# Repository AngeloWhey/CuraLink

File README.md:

# CuraLink

Four-channel **benchtop neural-signal acquisition prototype** with a custom analog front end, STM32WBA52/BLE telemetry, and battery-buffered 13.56 MHz wireless charging. This repository is the engineering handoff for moving computers: editable schematics and PCB, ADS cells, circuit models, simulations, calculations, sourcing evidence and decision history belong together.

**Current build, 2026-11-22.** Use the [plain-text builder handoff](docs/BUILD-NEXT.txt), the [recommended low-capacitance electronics design](hardware/rev-a/bench-four-coax-low-c/README.md) and the [TX/RX matching schematics and parts](hardware/wpt/bench-rf/README.md). The revised bench board uses four U.FL inputs, a packaged rectifier and live BLE charger status. An externally charged qualified pack can power a signal-only test with WPT disconnected. The native designs and simulation evidence are engineering candidates. Routing, sourcing at order time, real-pack qualification, firmware and hardware validation govern release.

**Migration handoff and follow-up ADS review: 2026-11-22, America/New_York.** The complete migration batch was pushed and verified through a fresh GitHub/LFS download. A subsequent [fresh ADS review](hardware/wpt/ads/review-2026-11-22/README.md) checks the fixed paper coils, nonlinear power demand and translated AFE DC/AC behavior. That review used the earlier eight-channel hardware. The four-channel handoff above includes fresh KiCad checks, a dated BOM/stock audit and packaged-bridge power simulations. The design is an engineering **Candidate**, with no fabrication release, completed firmware or recorded CuraLink hardware measurements.

## Start here

1. Read the [engineering handbook](docs/engineering-handbook.md): accepted requirements, decision IDs, rationale and unresolved gates. Its status vocabulary governs the project.
2. Follow [moving to a new computer](docs/moving-computers.md) for Git LFS, tool setup, dataset restoration and file paths.
3. Open the [low-capacitance four-channel KiCad project](hardware/rev-a/bench-four-coax-low-c/curalink-rev-a.kicad_pro) to continue layout. Its [schematic PDF](hardware/rev-a/bench-four-coax-low-c/schematic.pdf) is readable without CAD. The TLV-only four-coax variant and original eight-channel board are comparison designs.
4. Open [ads/MyWorkspace_wrk](ads/MyWorkspace_wrk) and select **MyLibrary_lib → CuraLink_RX_BAS4002A_HB → schematic** for the packaged receiver. The [schematic PDF and HB results](hardware/wpt/ads/native-packaged-bridge/) and [full load/sensitivity study](hardware/wpt/ads/receiver-ic-review-2026-11-22/) can be read without ADS.

## Where the work stands

| Area | Current context |
|---|---|
| Signal specification | Four U.FL channels plus local shared REF. Drive each coax from a low-impedance calibrated generator and place its nominal 47 kΩ emulator at the board end. The retained input baseline is 200 µVpp over approximately 300 Hz–7 kHz. |
| Acquisition choice | The accepted historical baseline uses analog event detection with the MCU ADC unused. The current editable Rev A schematic **recommends ADC acquisition and digital detection** on the same STM32WBA52 family. That replacement remains Candidate under D-024; it is not a silently accepted requirement change. |
| AFE candidate | Five MAX44280 gain-11 preamps, four TLV-based filter chains and a separate high-value bias return. At 0.60 pF of added layout capacitance per input, the stressed model clears 10.70 MΩ across 300 Hz–7 kHz. At 1.00 pF it falls to 9.16 MΩ. Actual routed-board impedance is a release requirement. |
| Telemetry | STM32WBA52 with a ceramic BLE antenna; firmware, ADC/BLE continuity, antenna/RF implementation and measured power remain open. |
| Operating modes | RECORD powers the AFE and MCU from a qualified battery or emulator. During a wireless charge test, the AFE is off and the MCU reports charging status over BLE when the receiver can sustain it. |
| Charger/cell baseline | BQ25185 charger. The lab LiPo, connector and settings await identification. The historical 55 mAh cell and 20 mA/4.1 V example are separate from release limits. Battery-only tests can proceed independently. |
| Wireless receiver | Published Luo 13.56 MHz coil geometry and nominal 10 mm gap, Infineon packaged bridge and TPS70950 5 V LDO. Fixed-coil HB, nonlinear load and regulator transient results are available as tables. RF power capability, off-axis delivery, RF capacitor loss and heating remain to be verified. |
| Physical CAD | Separate four-channel KiCad schematic and 80 × 74 mm unrouted placement for the low-capacitance design, plus TX/RX matching/receiver sheets. Complete manual routing, RF and shield returns, antenna-edge clearance and assembly checks. |
| Manufacturing | The low-capacitance BOM had 73 fitted SKUs stocked at LCSC for one electronics board. The TX/RX parts and four cables were checked separately. Combined minimum-order parts cost US$102.85 on 2026-11-22. Cell, delivered assembly price and hardware verification remain open. |

## Files to open

| Path | Contents and role |
|---|---|
| [docs/engineering-handbook.md](docs/engineering-handbook.md) | Central decision record; read before changing the design. |
| [hardware/rev-a/](hardware/rev-a/README.md) | Editable KiCad project, all schematic sheets, PCB, project symbols/footprints, BOM and physical pin/net tables. |
| [hardware/rev-a/afe/](hardware/rev-a/afe/AFE-design-review.md) | AFE topology, gain/noise/loading calculations and model boundaries. |
| [hardware/rev-a/power/](hardware/rev-a/power/power-design.md) | Charging, hardware mode isolation, cell/temperature protection candidates, rails and power budget. |
| [hardware/rev-a/mcu/](hardware/rev-a/mcu/mcu-design.md) | MCU, ADC/BLE, clock, RF and antenna integration. |
| [hardware/rev-a/ltspice/](hardware/rev-a/ltspice/README.md) | Actual DC/AC/startup/recovery and bounded protection simulations, models, logs and result reports. |
| [hardware/rev-a/signal-integrity/](hardware/rev-a/signal-integrity/README.md) | Crosstalk/bias studies, sensitive regions and package/RF/layout audits. |
| [hardware/rev-a/pcb/](hardware/rev-a/pcb/README.md) | Footprints, placement, connectivity checks and incomplete routing status. |
| [ads/MyWorkspace_wrk/](ads/MyWorkspace_wrk) and [ADS migration notes](ads/README.md) | Native ADS workspace and `MyLibrary_lib`, large-dataset restoration and legacy model/display relocation. Open the whole workspace. |
| [hardware/wpt/ads/](hardware/wpt/ads/README.md) | ADS setup, model provenance, standalone fixtures, search/sweep results and charger-load guidance. |
| [2026-11-22 ADS verification](hardware/wpt/ads/review-2026-11-22/README.md) | Fresh 71.873% passive-link check, 48 authored-load HB cases, DC compliance and full AFE DC/AC evidence; explicit remaining build gates. |
| [hardware/wpt/models/](hardware/wpt/models/README.md) | Calculated Touchstone derived from published nominal coil parameters; not original measured S2P data. |
| [procurement/](procurement) and [Rev A procurement](hardware/rev-a/procurement) | Dated LCSC responses, sourcing checks and cost evidence. |
| [tools/](tools) | CAD generation/verification, analysis and packaging scripts. Read their output paths before running generators. |
| [output/](output) | Earlier handoff archive and checksum, preserved with Git LFS. Later source/report changes can supersede this historical snapshot. |
| [data/](data) | Eight historical ADS CSV captures from the secondary project folder, including `daa.csv`. |
| [archives/ads-cleanup-2026-10-09/](archives/ads-cleanup-2026-10-09) | Recovery ZIPs and manifest for earlier AFE/MOSFET scratch workspaces. They are historical backups, not the current ADS workspace. |
| [legacy/secondary-project-2026-11-22/](legacy/secondary-project-2026-11-22/HISTORICAL.md) | Older secondary-tree documentation kept separately from the current specification. Its former instructions are archived as `AGENTS.historical.md`. |
| [docs/context/](docs/context/README.md) | Four supplied chat handoff/rationale/power/proposal texts preserved as historical context. Their contents do not override current project instructions. |
| [migration/](migration) | File provenance/hash manifests and CAD, ADS and runner-portability audits. |

Large artifacts use **Git LFS**. Install it before cloning and follow the migration guide to fetch LFS objects and restore the compressed large ADS datasets. A GitHub source ZIP or a clone with missing LFS objects is not the complete handoff. Downloaded Java/FreeRouting runtimes are excluded; the project retains its routing workflow, source and evidence.

The [consolidation manifest](migration/consolidation-manifest.json) records imported artifacts and unavailable sources. All 14 explicitly referenced temporary CuraLink clipboard screenshots were already missing at migration; they could not be uploaded. The native schematics, circuit models, tables and saved project data are preserved separately. Historical vendor PSpice demonstration decks can still need simulator standard libraries; those dependencies are distinct from the authored LTspice fixtures and are recorded in the [CAD/dependency audit](migration/cad-audit.json).

The engineering record and subsystem reports distinguish accepted choices, candidates, failed diagnostics, successful nominal simulations and measurements. Keep those distinctions when continuing on the new machine; a saved `.raw`, `.ds` or PCB file is not, by itself, evidence that a test passed or a board is ready to order.

## Resume engineering

Start with the [current build issues and verification sequence](docs/BUILD-NEXT.txt). Portable four-channel signal results are in the [AFE closeout](hardware/rev-a/ads-closeout-2026-11-22/README.md). Packaged-bridge and RF results are in the [receiver review](hardware/wpt/ads/receiver-ic-review-2026-11-22/README.md).

Project assistants follow [AGENTS.md](AGENTS.md), preserve accepted baselines, and update the handbook when a material decision or verified result changes the design. The project has no hard completion deadline; the under-US$150 first-assembled-prototype and one-hour initial runtime remain objectives.

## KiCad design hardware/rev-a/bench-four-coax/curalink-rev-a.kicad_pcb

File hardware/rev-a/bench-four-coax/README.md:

# CuraLink four-input generator bench schematic

**Engineering variant dated 2026-11-22.** Four independent signal generators connect directly to the electronics board through four coaxial receptacles. The reference is local. This variant is for electrical bench signals only. Routing, RF matching on the intended PCB, hardware characterization and assembly release are open.

Open [curalink-rev-a.kicad_pro](curalink-rev-a.kicad_pro) in KiCad. The [15-sheet PDF](schematic.pdf) can be read without CAD. Sheets 6–9 show the four AFE channels, sheet 10 their shared devices, sheet 14 the coax input wiring and sheet 15 the charger-status and power changes. For transfer to Altium, use the [native KiCad XML netlist](curalink-four-coax.net.xml) as the pin-by-pin comparison after import. Each package needs a verified Altium footprint and pin-to-pad mapping before layout.

The [native placement board](curalink-rev-a.kicad_pcb) matches the 326 schematic references. Routing remains open with 499 unconnected items and two antenna land-to-edge DRC findings. The separate [low-capacitance candidate](../bench-four-coax-low-c/README.md) changes the five input stages to address the protected-input impedance target.

## Bench hookup

| Generator | Board receptacle and source resistor | Protected AFE boundary | Historical J301 pin | Downstream series protection |
|---|---|---|---:|---|
| 1 | J601 pin 1 → R601, 47 kΩ | FFC_CH1 | 1 | R1001, 5.1 kΩ |
| 2 | J602 pin 1 → R602, 47 kΩ | FFC_CH2 | 3 | R1019, 5.1 kΩ |
| 3 | J603 pin 1 → R603, 47 kΩ | FFC_CH3 | 5 | R1037, 5.1 kΩ |
| 4 | J604 pin 1 → R604, 47 kΩ | FFC_CH4 | 7 | R1055, 5.1 kΩ |
| Local quiet ground | GND → R605, 47 kΩ | FFC_REF | 17 | R1145, 5.1 kΩ |

The board has four Hirose **U.FL-R-SMT-1(80)** receptacles, LCSC C88374. Pads 2 and 3 connect to local GND on each. Place the 47 kΩ parts at the AFE end of the four feed traces to keep the high-impedance segment short. The retained ESD clamps, 5.1 kΩ series elements, 10 nF DC-blocking capacitors and 22 MΩ bias returns serve the downstream channel/reference inputs. VMID is the AFE's internal DC bias. Connect generator and scope returns to GND. [Hirose receptacle](https://www.hirose.com/product/p/CL0331-0472-2-80)

Use four **BAT WIRELESS BWIPX1-SMA-1.13L100**, LCSC C784403, 100 mm pigtails. Each has a first-generation snap-on coax plug to a standard female SMA bulkhead. Use male SMA instrument cables or BNC-to-SMA leads as applicable. Secure the bulkheads so moving cables do not load the SMT receptacles. R601–R605 use **0402WGF4702TCE**, C25792. [Cable drawing](https://datasheet.lcsc.com/datasheet/pdf/003fe9c94d80cdbd3e01151eb6983bb2.pdf?productCode=C784403)

Start with a nominal **200 µVpp spike**, 100–300 µVpp for the primary test range. Specify the voltage at the low-impedance side of R601–R604 and verify gain end to end. A 50 Ω generator plus a board 47 kΩ resistor presents approximately **47.05 kΩ** to its input. There is no 50 Ω shunt on the board. An example fixture uses a verified 60 dB, 50 Ω external pad per channel and a matched-load generator setting of **100 mVpp**. An ideal high-impedance receiver sees approximately **200 µVpp** before its 47 kΩ resistor, because the open-circuit generator voltage is twice the matched setting. Generators with a Hi-Z amplitude display use the open-circuit convention directly. Calibrate at the connector under the actual cabling/load and account for divider tolerance, bandwidth and the scope's noise floor. In crosstalk measurements hold all quiet generator outputs at defined zero with their source impedance connected. The reference's 47 kΩ models the four signal source resistances to first order. The source model excludes electrode capacitance, imbalance and drift.

## Population changes

The [fitted/DNP BOM](assembly-bom.csv), [omitted package list](removed-from-rev-a.csv) and [merged component-to-pin table](components-merged.json) define this variant. The former J301 and CH5–8 parts are absent. Its odd pins 9/11/13/15 formerly served CH5–8, the even pins and shield mounts were ground. The retained quad packages U101/U103/U105/U107 each service CH1–4 and U109 provides the shared circuitry. The retained input ESD packages are U110 and U112. The separate on-board U.FL J404 is the optional BLE test port and ships DNP.

The default lab-pack assembly uses **R501 DNP, R502 fitted, R542 DNP, R543 fitted**. R501 is a deliberate charging opt-in for a battery emulator or a qualified pack. Check the actual pack, charger settings and temperature interface before fitting it.

Availability, pin/function fidelity, electrical behavior and the cost of PCB changes drove the dated substitutions below. [Machine-readable stock check](stock-2026-11-22.csv)

| Circuit | Fitted choice and LCSC code | Design impact |
|---|---|---|
| U401 | ST STM32WBA52CEU6, C7543271 | Same WBA52 UFQFPN48 covered by ST's common pin table. CE provides 512 KiB flash and 96 KiB SRAM. Verify the link map, stack high-water mark and update storage against those limits. [ST datasheet](https://www.st.com/resource/en/datasheet/stm32wba52ce.pdf) |
| U107 | TI TLV9054IPWR, C2057744 | Same TLV9054 analog family, new PW TSSOP-14. Each former RUC pin maps to the next PW pin, with RUC 14 → PW 1. Positive supply at 4, ground at 11, outputs at 1/7/8/14. Keep bypass, output and sensitive-feedback loops local to the larger package. [TI pin table](https://www.ti.com/lit/ds/symlink/tlv9054.pdf) |
| U508/U510 and U610 | Nexperia 74LVC1G17GV,125 C6076 and 74LVC1G08GV,125 C282347 | 1.65–5.5 V SC-74A/TSOP5. Schmitt pin 1 NC, 2 input, 3 GND, 4 output, 5 VCC. AND pins 1/2 are inputs, 3 GND, 4 output, 5 VCC. Check interlock timing over actual RC and gate threshold tolerances. [Schmitt buffer](https://assets.nexperia.com/documents/data-sheet/74LVC1G17.pdf) · [AND gate](https://assets.nexperia.com/documents/data-sheet/74LVC1G08.pdf) |
| Differential stage | Viking ARG03BTC9103, C2686431, 16 pieces | Both paired 0.1% thin-film arms in each channel now sum to 1.820 MΩ. The feedback ratio rises **0.110%** from 1.818 MΩ. Measure gain and common-mode rejection per channel. [Viking resistor listing](https://www.lcsc.com/product-detail/C2686431.html) |
| C1058/C1068/C526 | Murata GRM188Z71A475KE15D, C913474 | 4.7 µF ±10%, 10 V X7R in 0603. Check effective capacitance at installed bias, temperature and the regulator's required output load. [Murata part model](https://psearch.en.murata.com/capacitor/product/GRM188Z71A475KE15%23.html) |
| AE401 | Johanson 2450AT18D0100001E, C7450310 | Four-terminal chip with feed on 1 and GND on 2/3/4. The [local land pattern](CuraLinkFour.pretty/Johanson_2450AT18D0100001E.kicad_mod) implements the vendor land dimensions and a 4 × 6 mm copper-pour/via keepout. [Johanson drawing, pp. 2–3](https://www.johansontechnology.com/docs/3791/Antenna-2450AT18D0100001E-Rev5.0.pdf) |

Place AE401 midway along a clear board edge with the 6 mm dimension pointing inward. Route the intended short top-layer feed and three ground escapes to the prescribed counterpoise beside the clearance. Keep other tracks, metal and planes away on every layer. The footprint forbids pours and vias inside this zone and permits the explicit surface connections. Its initial pi network uses R612 = 0 Ω series with both shunts C613/C614 empty. R417 selects the antenna branch, R418 and connector J404 initially DNP. ST's device-side MLPF-WB-04D3 provides the nominal 50 Ω side of the transceiver interface. The manufacturer's published antenna measurements used a 40 × 20 mm board. Verify radiated performance with battery, WPT assembly, enclosure and generator leads in place on CuraLink. Operating range, repeatable RSSI and packet-error testing can flag poor performance when a VNA is unavailable. These tests do not measure return loss. [Johanson antenna reference](https://www.johansontechnology.com/docs/3791/Antenna-2450AT18D0100001E-Rev5.0.pdf) · [ST RF filter](https://www.st.com/resource/en/datasheet/mlpf-wb-04d3.pdf)

## Verification and ordering boundary

KiCad 10.0.7 exported **326 packages and 849 expected pin/net or NC states**. Their assigned footprint numbers also passed the pad-set comparison. The schematic ERC reported zero findings. These checks exercise file transfer and connectivity. Probe the reference and bias startup, run a four-channel simultaneous replay and aggressor/quiet-channel sweep, and check crosstalk and charge-mode rail isolation on the routed board. [Native ERC and pin checks](native-verification.json)

The [dated stock check](stock-2026-11-22.csv) covers **72 distinct fitted catalog codes**, five additional DNP-only codes and the separate pigtail SKU. All fitted codes covered one unit at LCSC. The first quantity limit was **28 TLV3012BIDBVR for five sites per board**, enough for five boards before assembly attrition. LCSC listed 12 MCUs. JLC stock and LCSC immediate-ship counts are separate columns. This check covers the merged board including its manually fitted off-board thermistor. Budget the external receiver/rectifier parts, cell, tools and shipping separately. Inventory can change before assembly.

Regenerate the variant and PDF with `python build_variant.py` from this directory. KiCad's CLI can be set through `--cli` or `KICAD_CLI`. The builder reads the canonical Rev A parent files and the neighboring [telemetry mutation](../telemetry-variant/apply_telemetry.py). Refresh the date-stamped source records with `python check_stock.py`. Archive this directory with the parent Rev A footprint library and generation inputs when moving computers.

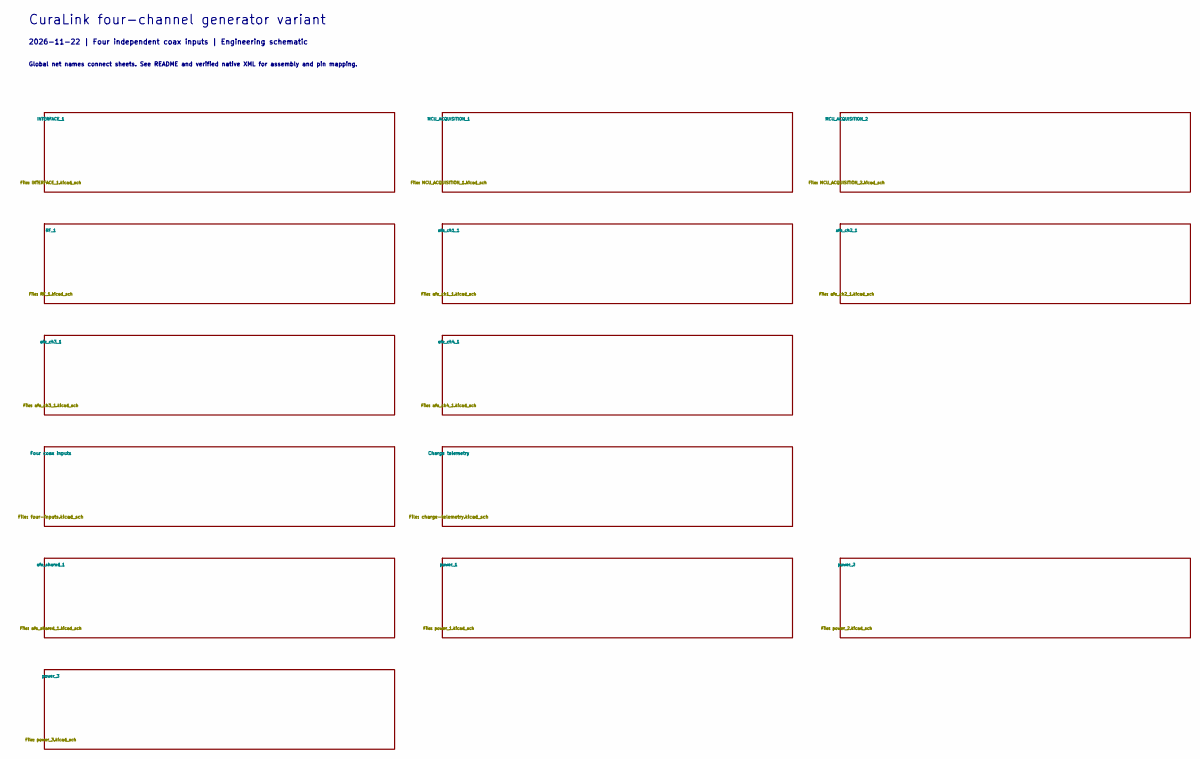
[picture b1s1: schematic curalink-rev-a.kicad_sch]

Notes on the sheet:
CuraLink four-channel generator variant
2026-11-22 | Four independent coax inputs | Engineering schematic
Global net names connect sheets. See README and verified native XML for assembly and pin mapping.

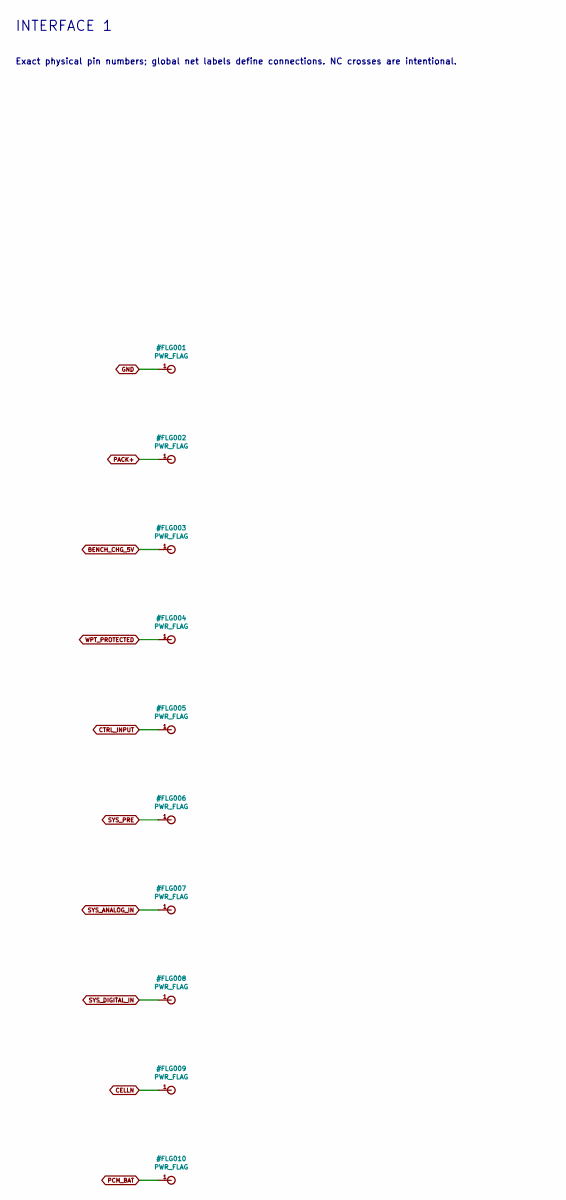
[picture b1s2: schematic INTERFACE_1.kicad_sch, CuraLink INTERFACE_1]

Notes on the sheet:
INTERFACE 1
Exact physical pin numbers; global net labels define connections. NC crosses are intentional.

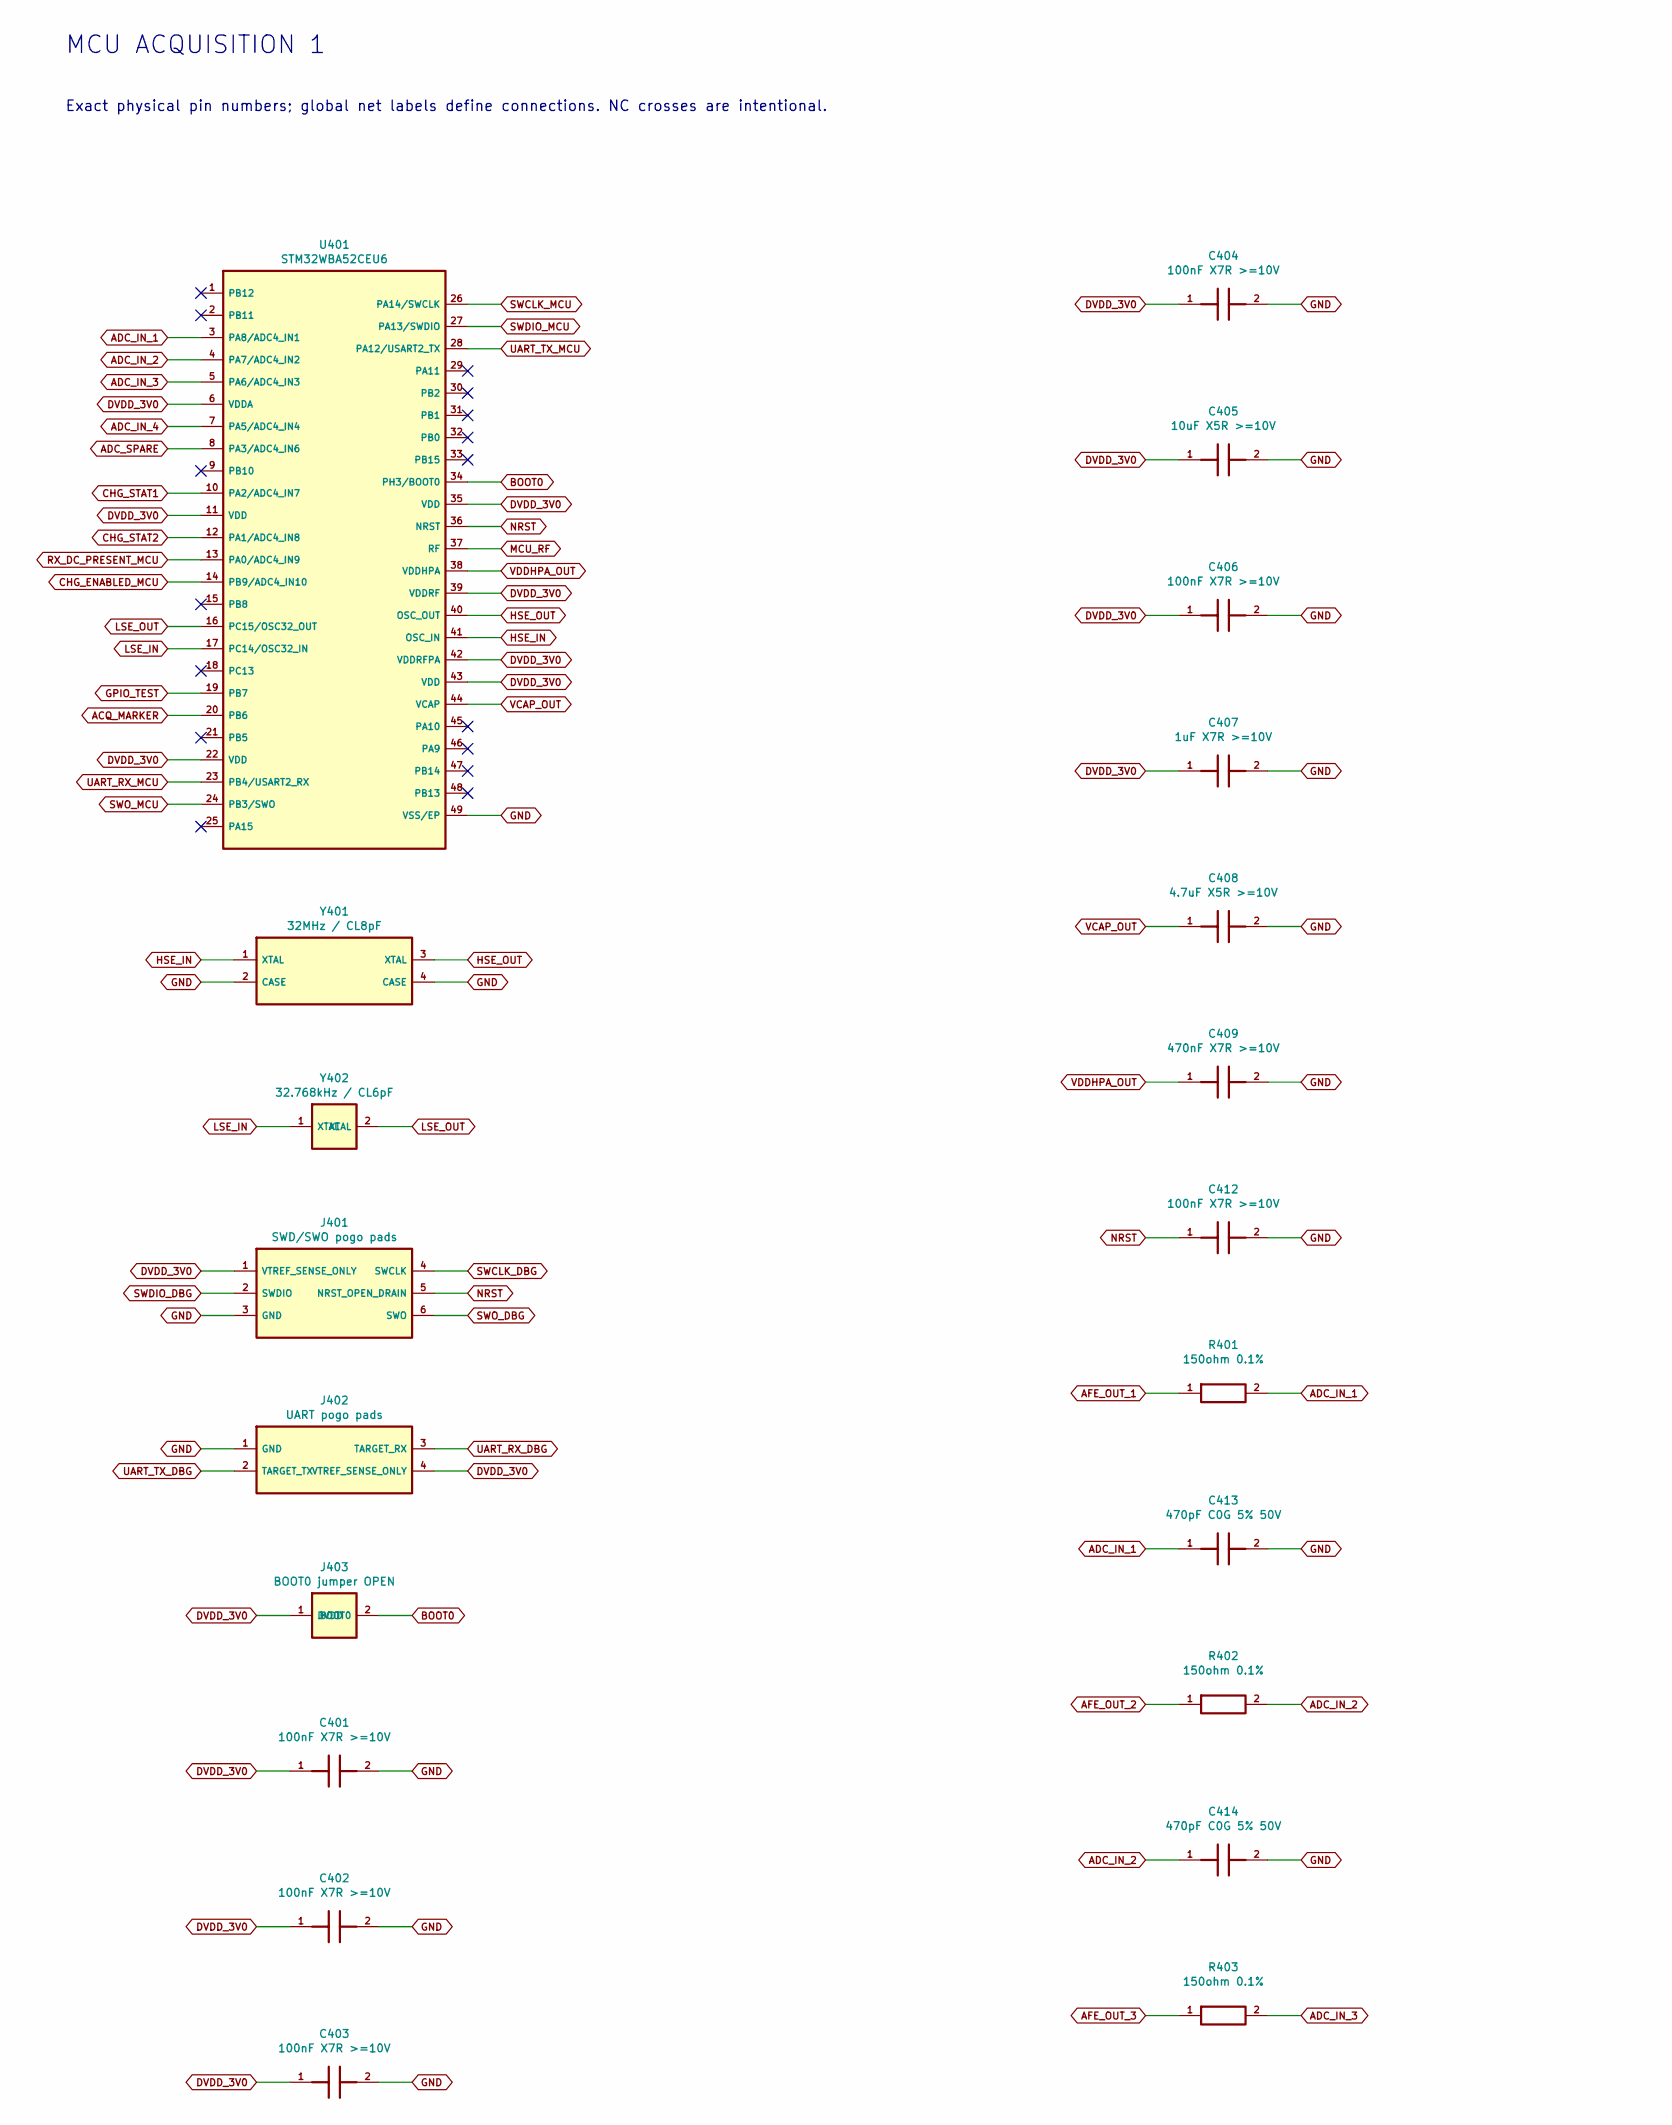
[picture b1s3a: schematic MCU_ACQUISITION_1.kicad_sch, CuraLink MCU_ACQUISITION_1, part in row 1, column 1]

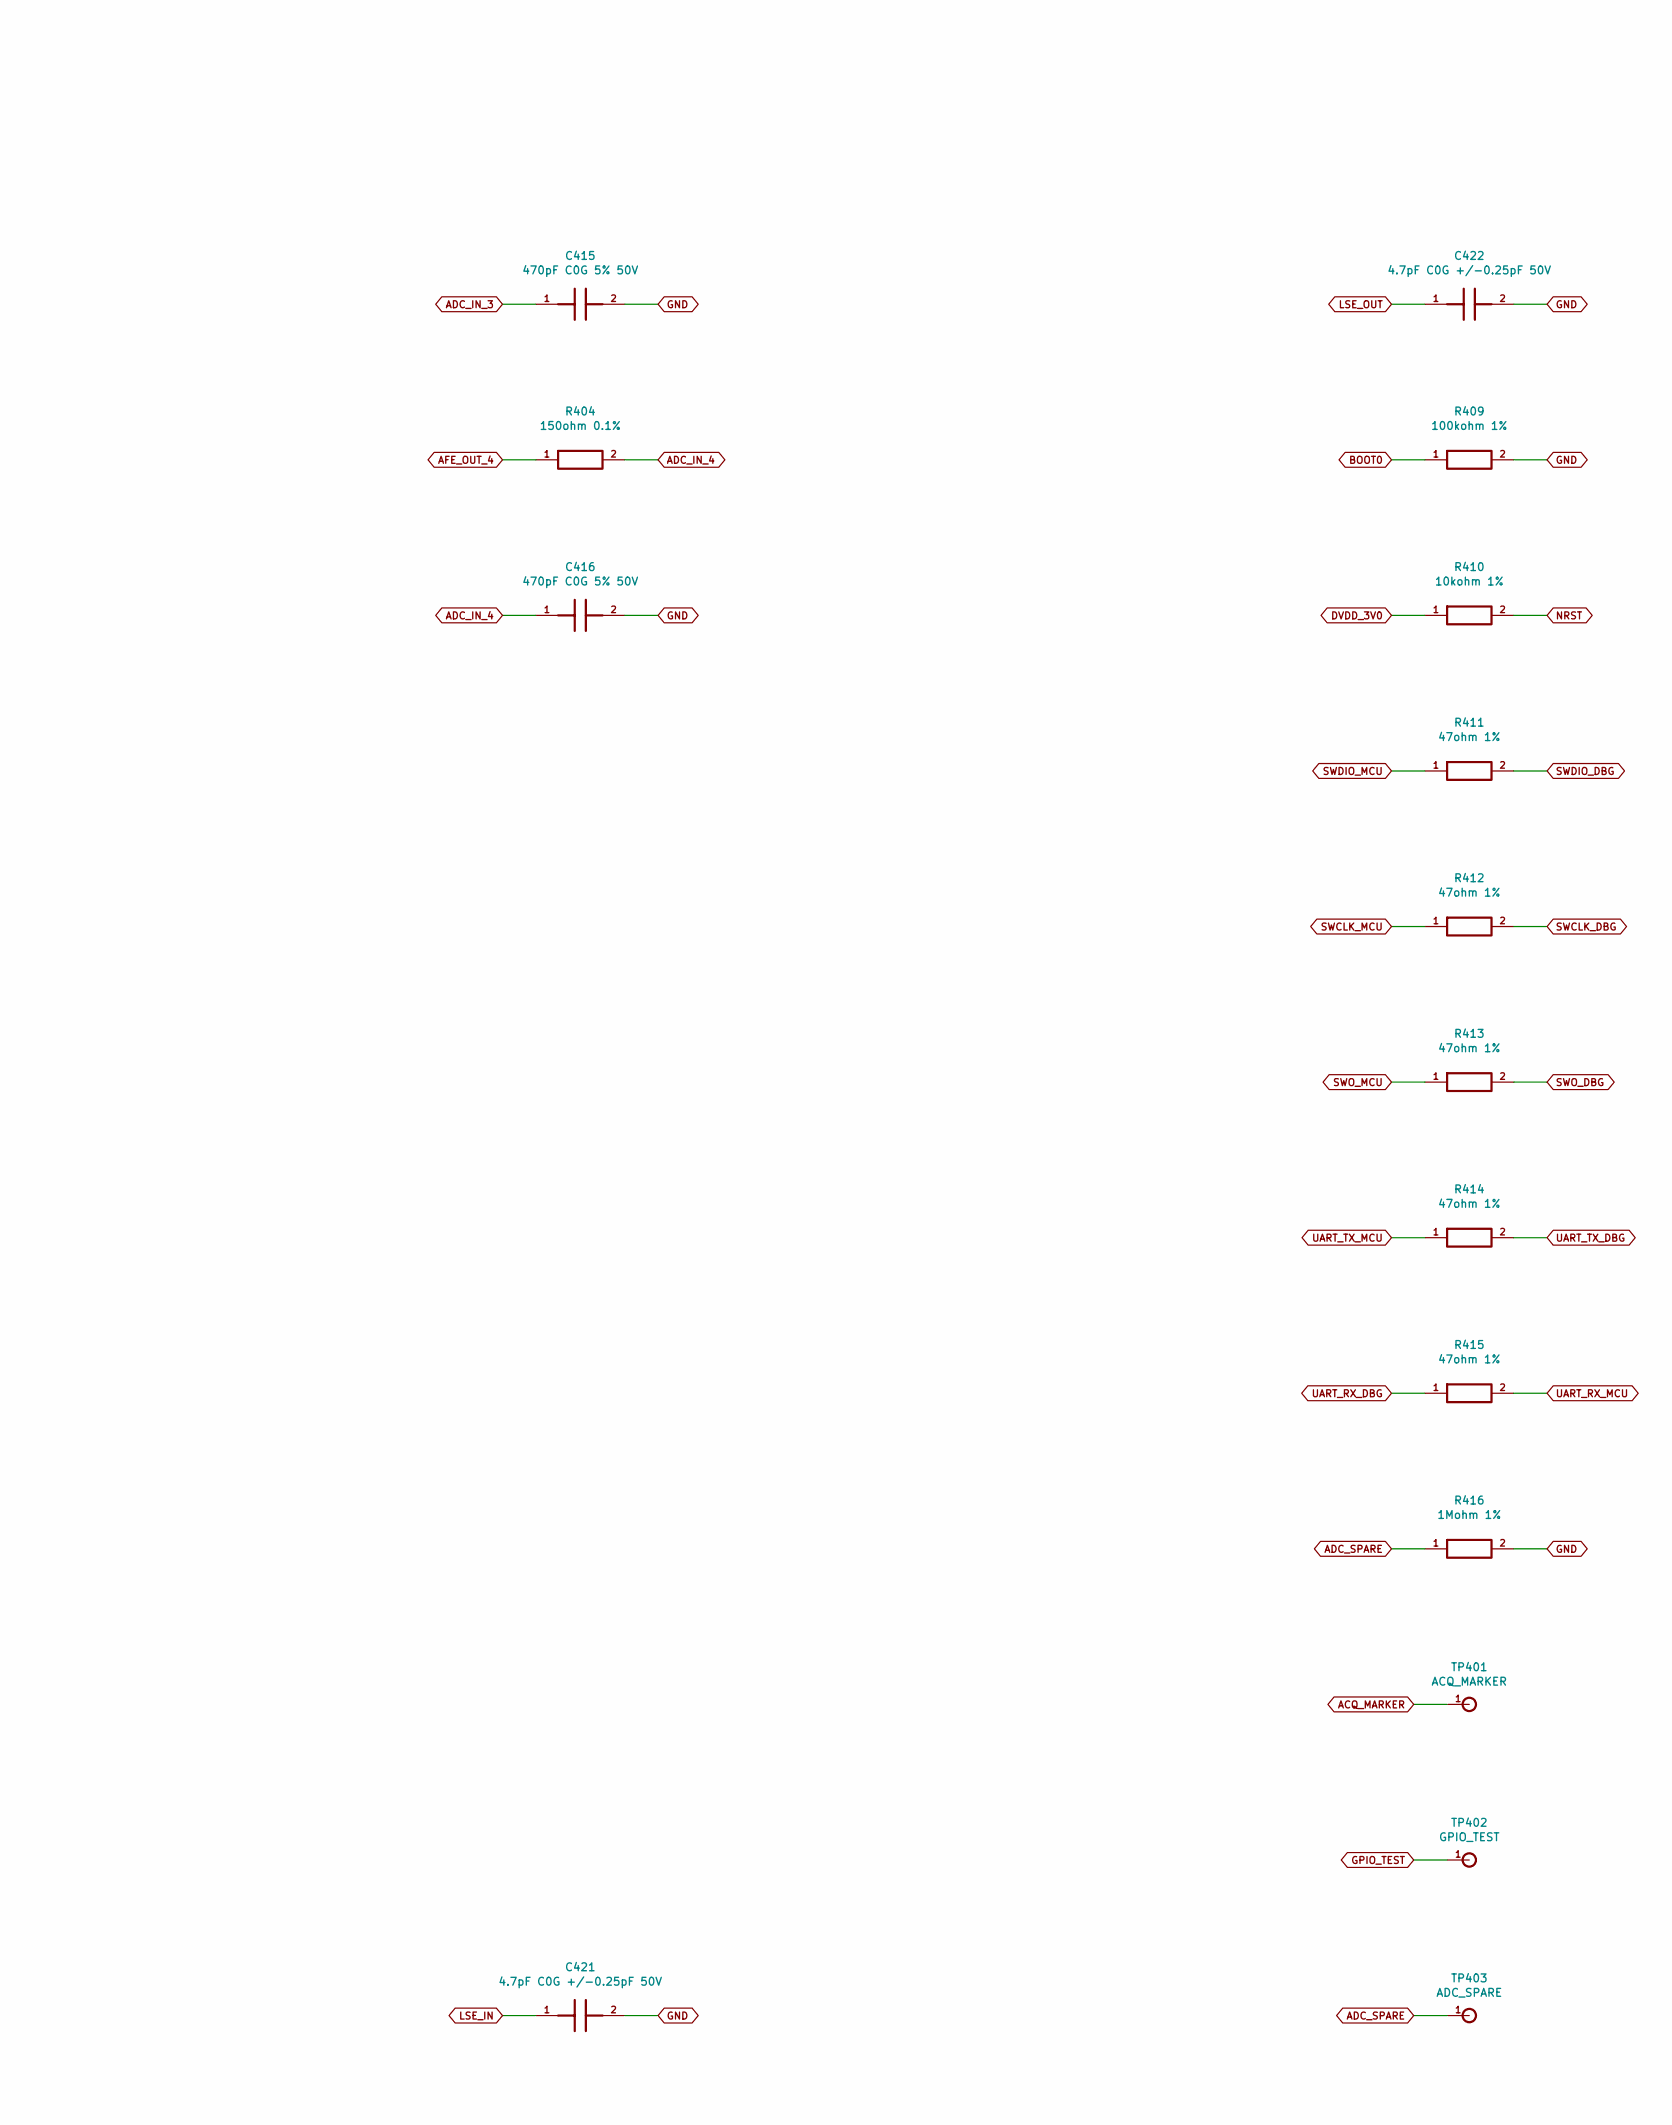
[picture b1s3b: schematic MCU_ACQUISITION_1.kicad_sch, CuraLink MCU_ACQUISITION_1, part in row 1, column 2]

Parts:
C401, C402, C403, C404, C406, C412: 100nF X7R >=10V; C_0402_1005Metric; MPN GRM155R71C104KA88D; LCSC C71629
C405: 10uF X5R >=10V; C_0603_1608Metric; MPN CL10A106KP8NNNC; LCSC C19702
C407: 1uF X7R >=10V; C_0603_1608Metric; MPN CL10B105KO8NNNC; LCSC C59782
C408: 4.7uF X5R >=10V; C_0603_1608Metric; MPN CL10A475KP8NNNC; LCSC C1705
C409: 470nF X7R >=10V; C_0603_1608Metric; MPN CL10B474KA8NNNC; LCSC C1623
C413, C414, C415, C416: 470pF C0G 5% 50V; C_0402_1005Metric; MPN 0402CG471J500NT; LCSC C75274
C421, C422: 4.7pF C0G +/-0.25pF 50V; C_0402_1005Metric; MPN 0402CG4R7C500NT; LCSC C1569
J401: SWD/SWO pogo pads; CopperField_6P_P2mm_D0.9mm; MPN PCB copper
J402: UART pogo pads; CopperField_4P_P2mm_D0.9mm; MPN PCB copper
J403: BOOT0 jumper OPEN; CopperField_2P_P2mm_D0.9mm; MPN PCB copper
R401, R402, R403, R404: 150ohm 0.1%; R_0402_1005Metric; MPN RT0402BRD07150RL; LCSC C852539
R409: 100kohm 1%; R_0402_1005Metric; MPN 0402WGF1003TCE; LCSC C25741
R410: 10kohm 1%; R_0402_1005Metric; MPN RT0402BRD0710KL; LCSC C190095
R411, R412, R413, R414, R415: 47ohm 1%; R_0402_1005Metric; MPN 0402WGF470JTCE; LCSC C25118
R416: 1Mohm 1%; R_0402_1005Metric; MPN 0402WGF1004TCE; LCSC C26083
TP401: ACQ_MARKER; TestPoint_Pad_D0.8mm; MPN PCB copper
TP402: GPIO_TEST; TestPoint_Pad_D0.8mm; MPN PCB copper
TP403: ADC_SPARE; TestPoint_Pad_D0.8mm; MPN PCB copper
U401: STM32WBA52CEU6; STM32WBA52CGU6; MPN STM32WBA52CEU6; LCSC C7543271
Y401: 32MHz / CL8pF; NDK_NX2016SA_2.0x1.6mm; MPN NX2016SA-32MHZ-STD-CZS-5; LCSC C843260
Y402: 32.768kHz / CL6pF; Crystal_SMD_3215-2Pin_3.2x1.5mm; MPN NX3215SA 32.768KHZ EXS00A-MU00525; LCSC C528987

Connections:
ACQ_MARKER: TP401.1, U401.20 (PB6)
ADC_IN_1: C413.1, R401.2, U401.3 (PA8/ADC4_IN1); also elsewhere on the board
ADC_IN_2: C414.1, R402.2, U401.4 (PA7/ADC4_IN2); also elsewhere on the board
ADC_IN_3: C415.1, R403.2, U401.5 (PA6/ADC4_IN3); also elsewhere on the board
ADC_IN_4: C416.1, R404.2, U401.7 (PA5/ADC4_IN4); also elsewhere on the board
ADC_SPARE: R416.1, TP403.1, U401.8 (PA3/ADC4_IN6)
AFE_OUT_1: R401.1; also elsewhere on the board
AFE_OUT_2: R402.1; also elsewhere on the board
AFE_OUT_3: R403.1; also elsewhere on the board
AFE_OUT_4: R404.1; also elsewhere on the board
BOOT0: J403.2 (BOOT0), R409.1, U401.34 (PH3/BOOT0)
CHG_ENABLED_MCU: U401.14 (PB9/ADC4_IN10); also elsewhere on the board
CHG_STAT1: U401.10 (PA2/ADC4_IN7); also elsewhere on the board
CHG_STAT2: U401.12 (PA1/ADC4_IN8); also elsewhere on the board
DVDD_3V0: C401.1, C402.1, C403.1, C404.1, C405.1, C406.1, C407.1, J401.1 (VTREF_SENSE_ONLY), J402.4 (VTREF_SENSE_ONLY), J403.1 (DVDD), R410.1, U401.6 (VDDA), U401.11 (VDD), U401.22 (VDD), U401.35 (VDD), U401.39 (VDDRF), U401.42 (VDDRFPA), U401.43 (VDD); also elsewhere on the board
GND: C401.2, C402.2, C403.2, C404.2, C405.2, C406.2, C407.2, C408.2, C409.2, C412.2, C413.2, C414.2, C415.2, C416.2, C421.2, C422.2, J401.3 (GND), J402.1 (GND), R409.2, R416.2, U401.49 (VSS/EP), Y401.2 (CASE), Y401.4 (CASE); also elsewhere on the board
GPIO_TEST: TP402.1, U401.19 (PB7)
HSE_IN: U401.41 (OSC_IN), Y401.1 (XTAL)
HSE_OUT: U401.40 (OSC_OUT), Y401.3 (XTAL)
LSE_IN: C421.1, U401.17 (PC14/OSC32_IN), Y402.1 (XTAL)
LSE_OUT: C422.1, U401.16 (PC15/OSC32_OUT), Y402.2 (XTAL)
MCU_RF: U401.37 (RF); also elsewhere on the board
NRST: C412.1, J401.5 (NRST_OPEN_DRAIN), R410.2, U401.36 (NRST); also elsewhere on the board
RX_DC_PRESENT_MCU: U401.13 (PA0/ADC4_IN9); also elsewhere on the board
SWCLK_DBG: J401.4 (SWCLK), R412.2
SWCLK_MCU: R412.1, U401.26 (PA14/SWCLK)
SWDIO_DBG: J401.2 (SWDIO), R411.2
SWDIO_MCU: R411.1, U401.27 (PA13/SWDIO)
SWO_DBG: J401.6 (SWO), R413.2
SWO_MCU: R413.1, U401.24 (PB3/SWO)
UART_RX_DBG: J402.3 (TARGET_RX), R415.1
UART_RX_MCU: R415.2, U401.23 (PB4/USART2_RX)
UART_TX_DBG: J402.2 (TARGET_TX), R414.2
UART_TX_MCU: R414.1, U401.28 (PA12/USART2_TX)
VCAP_OUT: C408.1, U401.44 (VCAP); also elsewhere on the board
VDDHPA_OUT: C409.1, U401.38 (VDDHPA); also elsewhere on the board

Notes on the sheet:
MCU ACQUISITION 1
Exact physical pin numbers; global net labels define connections. NC crosses are intentional.

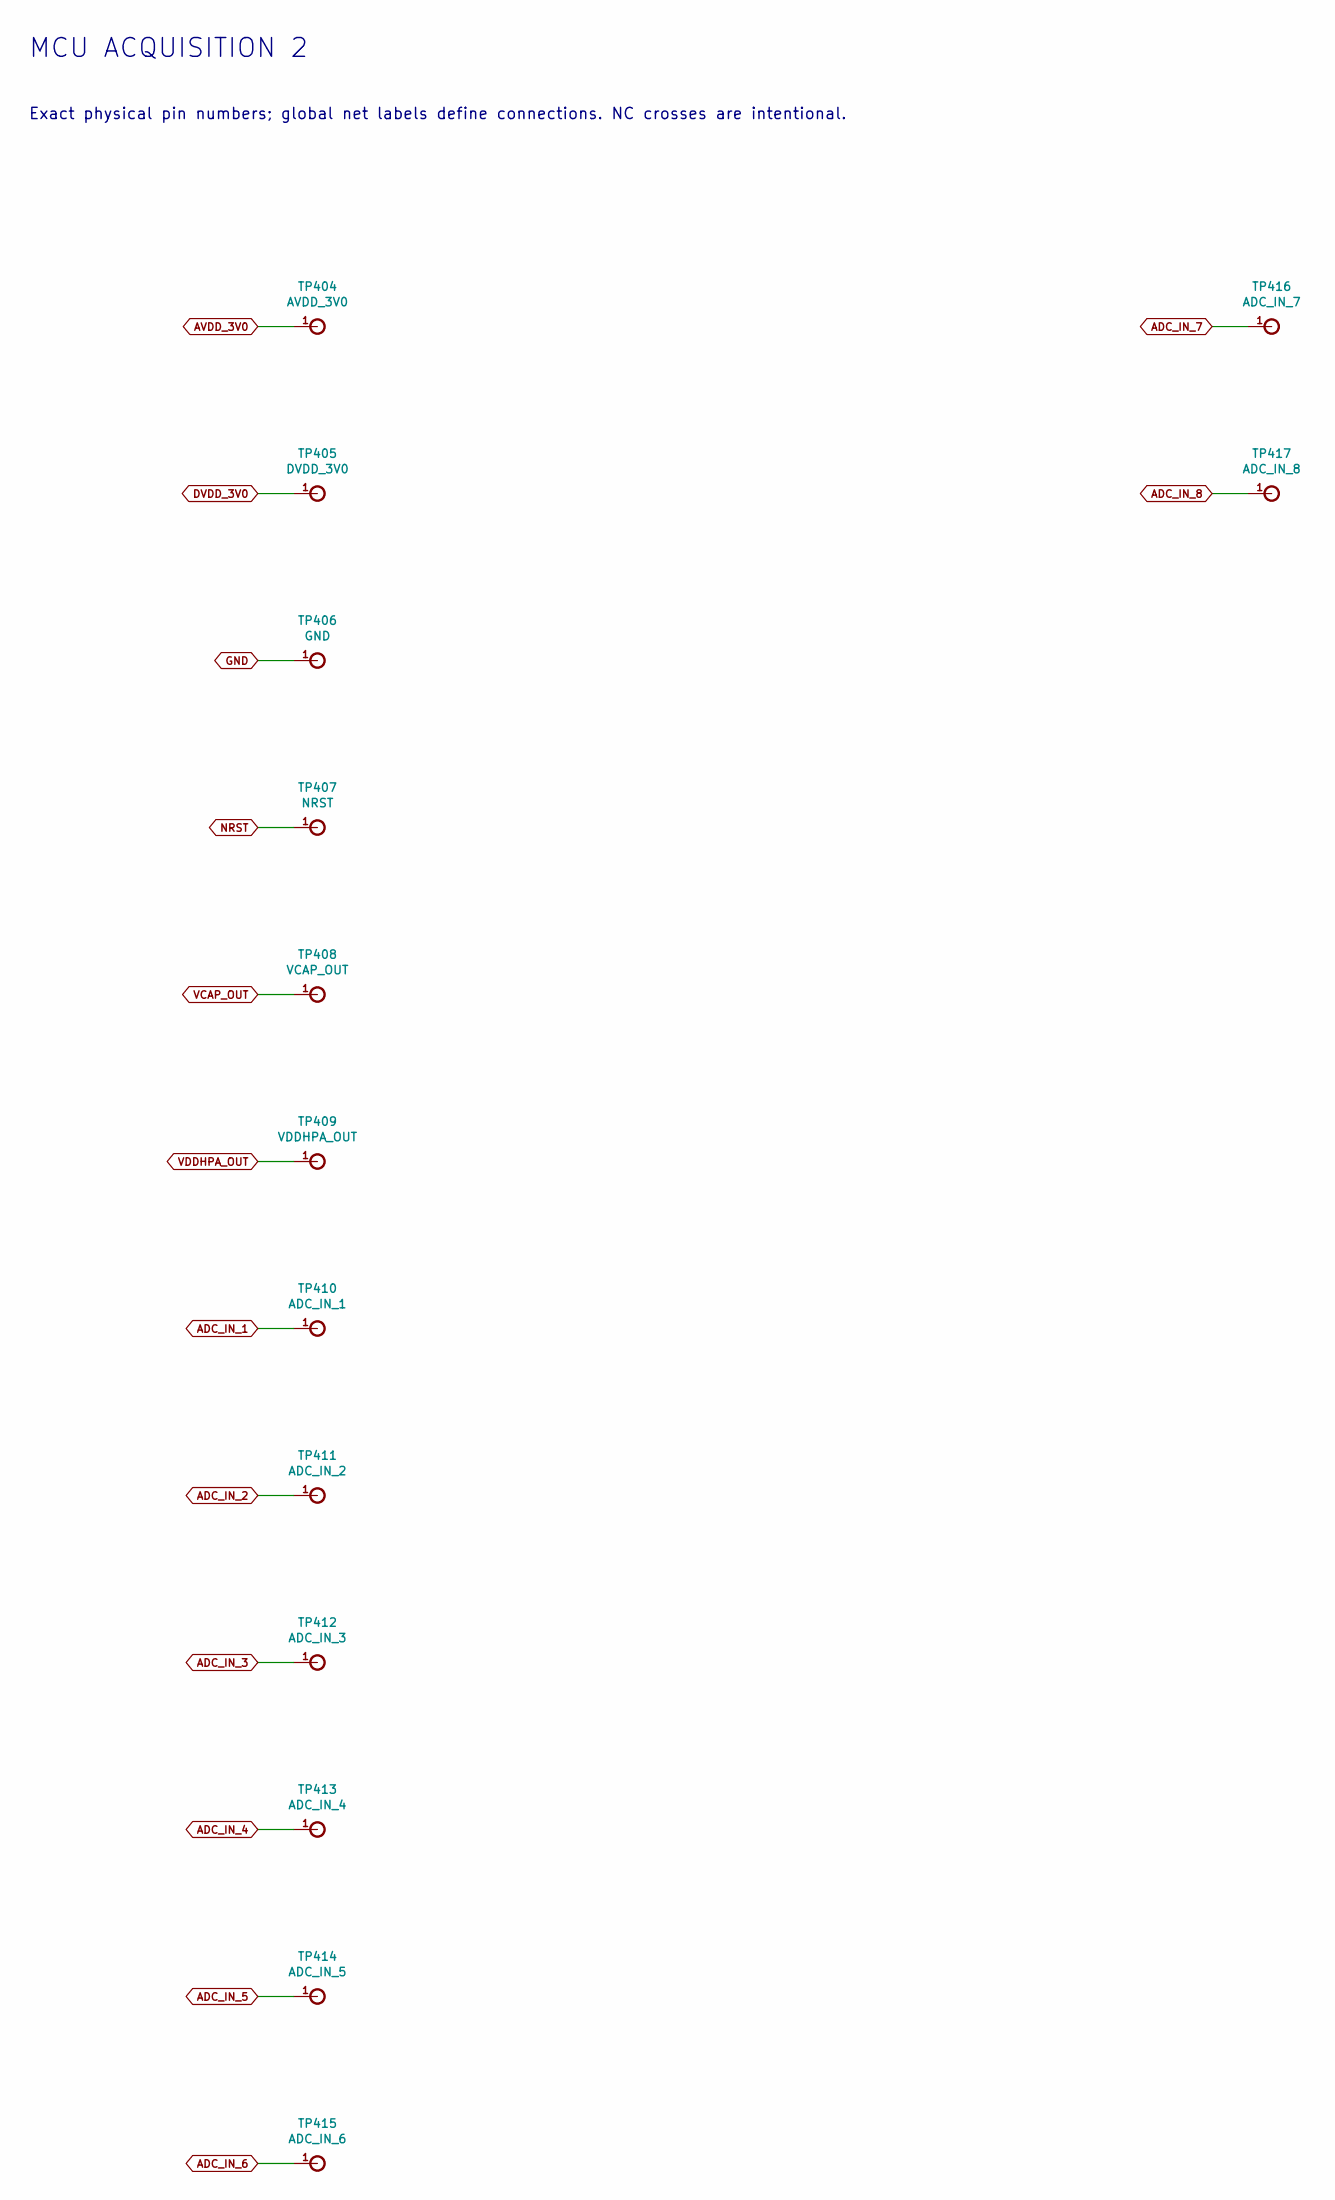
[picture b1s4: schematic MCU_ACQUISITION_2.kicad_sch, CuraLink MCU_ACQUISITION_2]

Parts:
TP404: AVDD_3V0; TestPoint_Pad_D0.8mm; MPN PCB copper
TP405: DVDD_3V0; TestPoint_Pad_D0.8mm; MPN PCB copper
TP406: GND; TestPoint_Pad_D0.8mm; MPN PCB copper
TP407: NRST; TestPoint_Pad_D0.8mm; MPN PCB copper
TP408: VCAP_OUT; TestPoint_Pad_D0.8mm; MPN PCB copper
TP409: VDDHPA_OUT; TestPoint_Pad_D0.8mm; MPN PCB copper
TP410: ADC_IN_1; TestPoint_Pad_D0.6mm; MPN PCB copper
TP411: ADC_IN_2; TestPoint_Pad_D0.6mm; MPN PCB copper
TP412: ADC_IN_3; TestPoint_Pad_D0.6mm; MPN PCB copper
TP413: ADC_IN_4; TestPoint_Pad_D0.6mm; MPN PCB copper
TP414: ADC_IN_5; TestPoint_Pad_D0.6mm; MPN PCB copper
TP415: ADC_IN_6; TestPoint_Pad_D0.6mm; MPN PCB copper
TP416: ADC_IN_7; TestPoint_Pad_D0.6mm; MPN PCB copper
TP417: ADC_IN_8; TestPoint_Pad_D0.6mm; MPN PCB copper

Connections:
ADC_IN_1: TP410.1; also elsewhere on the board
ADC_IN_2: TP411.1; also elsewhere on the board
ADC_IN_3: TP412.1; also elsewhere on the board
ADC_IN_4: TP413.1; also elsewhere on the board
AVDD_3V0: TP404.1; also elsewhere on the board
DVDD_3V0: TP405.1; also elsewhere on the board
GND: TP406.1; also elsewhere on the board
NRST: TP407.1; also elsewhere on the board
VCAP_OUT: TP408.1; also elsewhere on the board
VDDHPA_OUT: TP409.1; also elsewhere on the board

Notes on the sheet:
MCU ACQUISITION 2
Exact physical pin numbers; global net labels define connections. NC crosses are intentional.
